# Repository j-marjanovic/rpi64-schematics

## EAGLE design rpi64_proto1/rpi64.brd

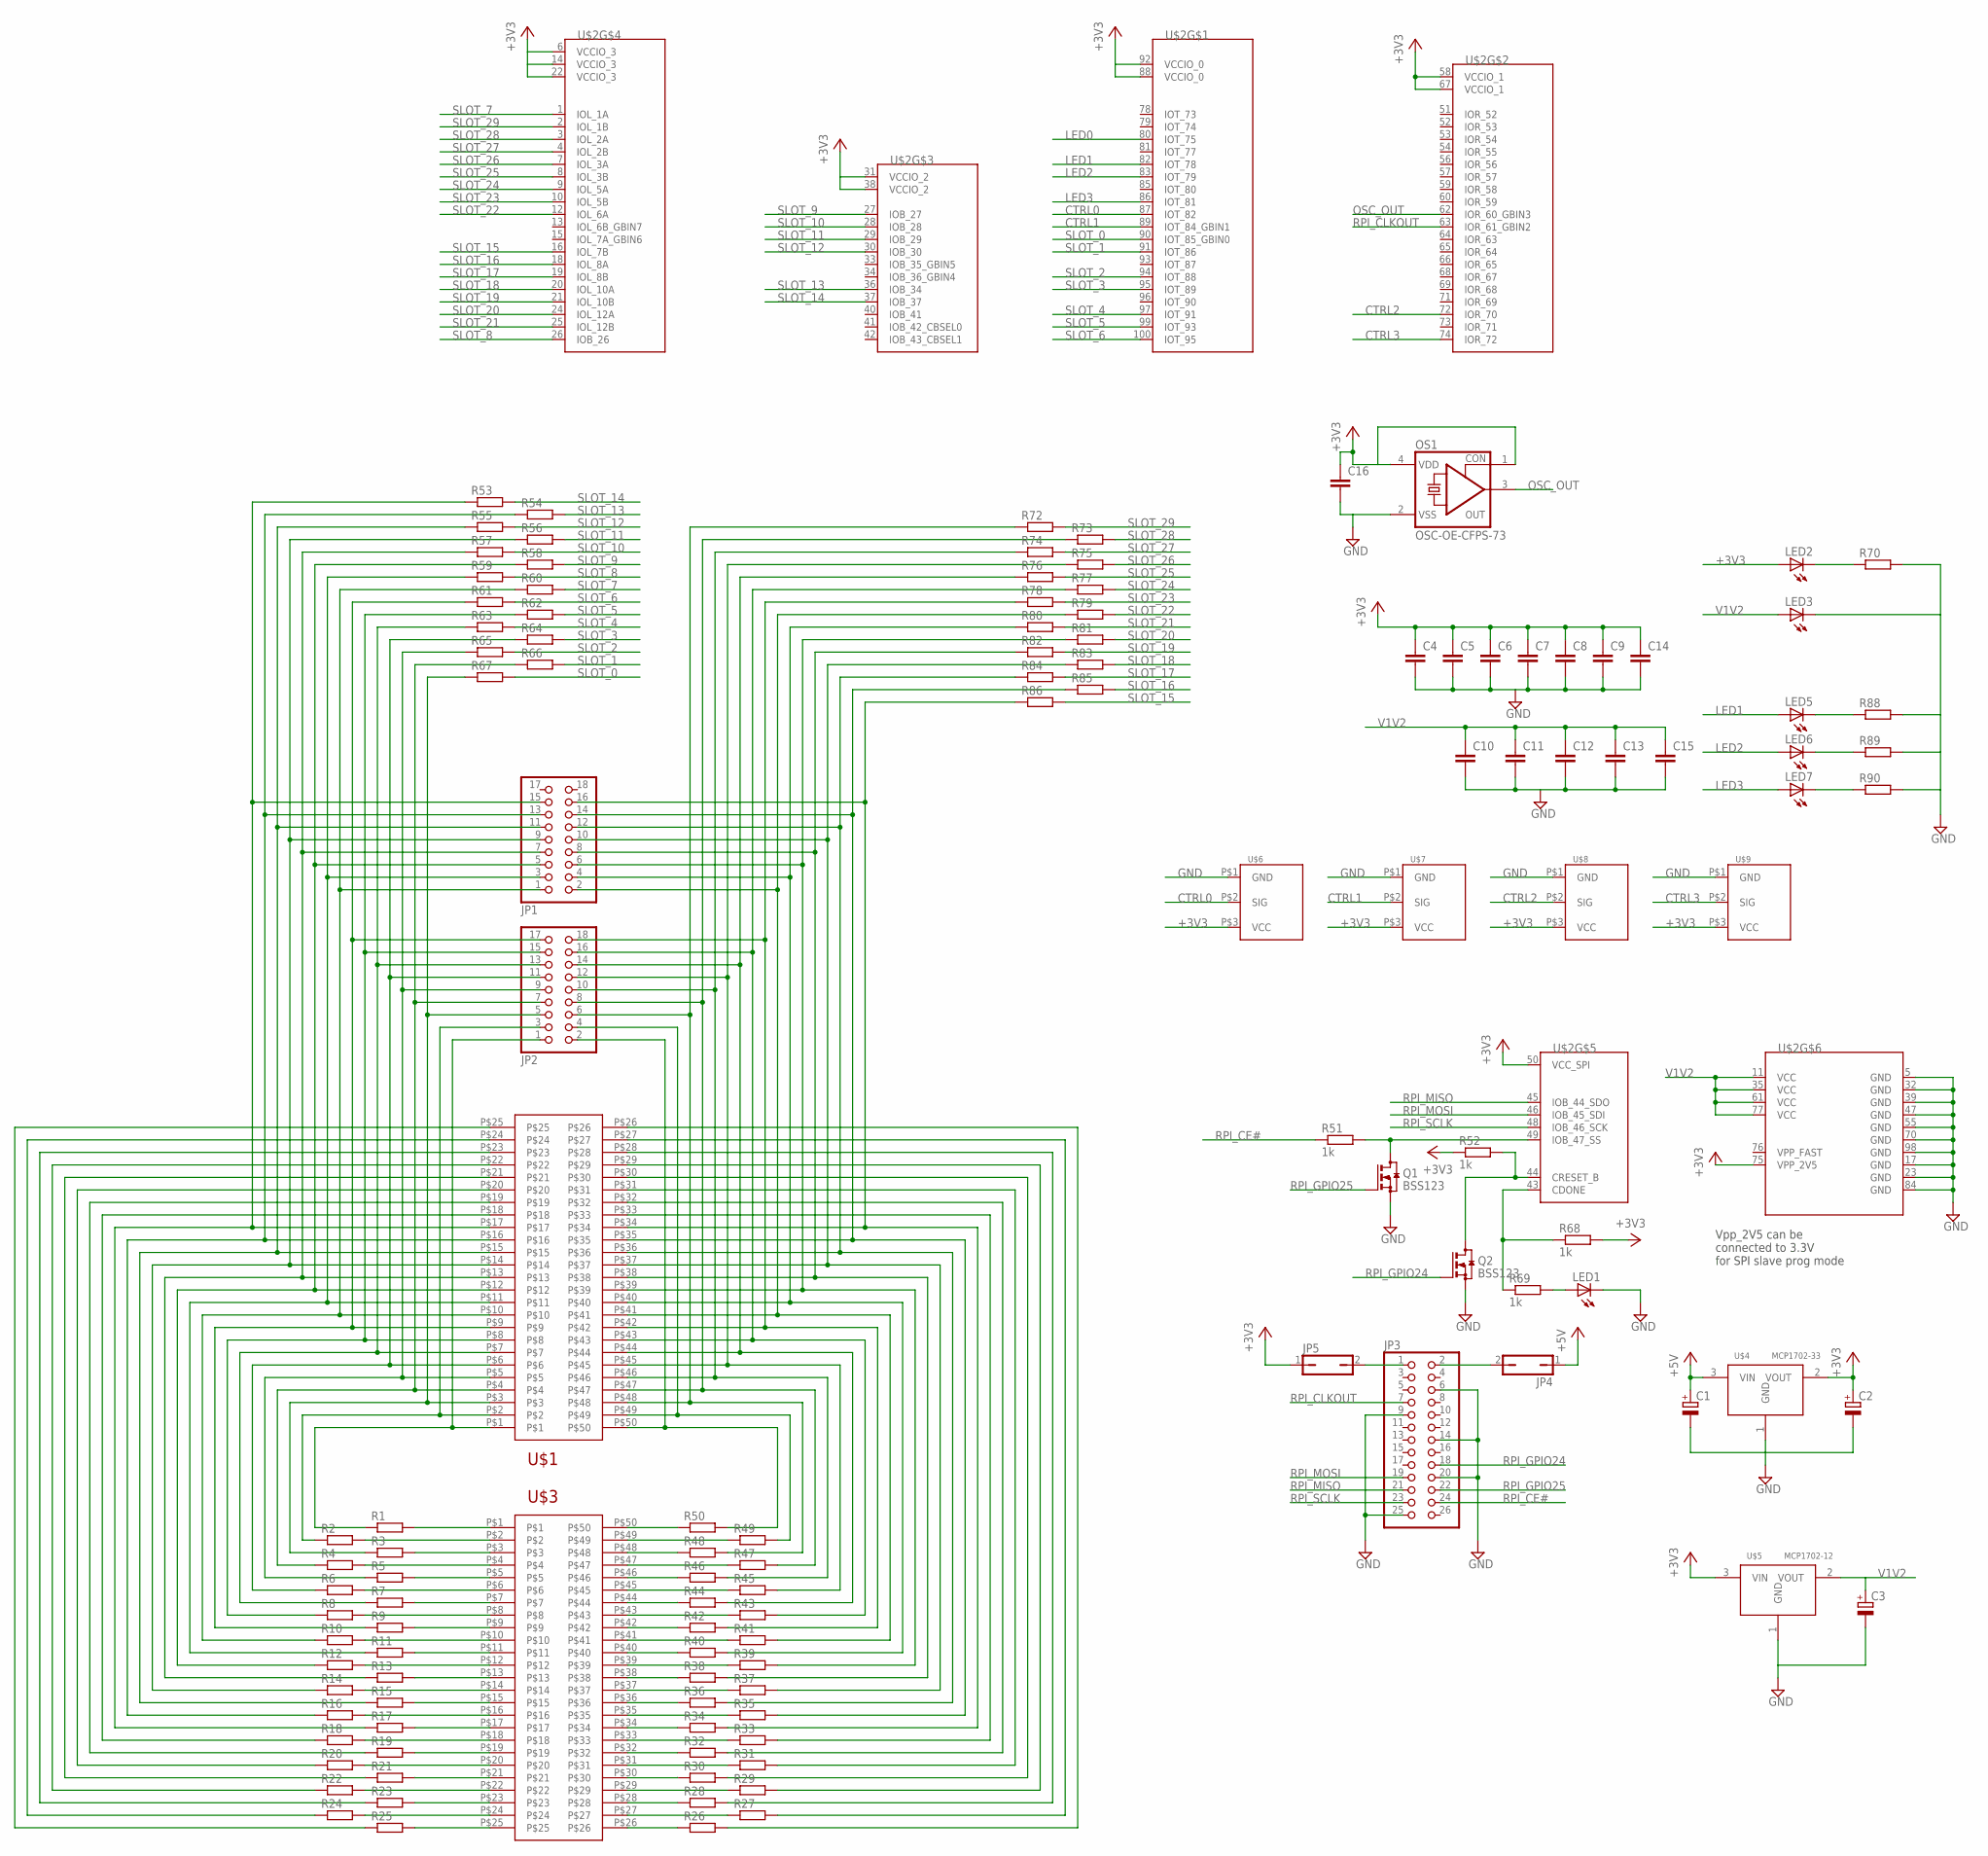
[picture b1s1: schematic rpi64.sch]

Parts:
C1, C2, C3: CPOL-EUR/2012-12R; R/2012-12R
C4, C5, C6, C7, C8, C9, C10, C11, C12, C13, C14, C15, C16: C-EUC0805; C0805
JP1, JP2: PINHD-2X9; 2X09
JP3: PINHD-2X13; 2X13
JP4, JP5: JP1Q; JP1
LED1, LED2, LED3, LED5, LED6, LED7: LEDCHIPLED_0603; CHIPLED_0603
OS1: OSC-OE-CFPS-73; 7.2X5.2-4-PAD
Q1, Q2: BSS123; SOT23
R1, R2, R3, R4, R5, R6, R7, R8, R9, R10, R11, R12, R13, R14, R15, R16, R17, R18, R19, R20, R21, R22, R23, R24, R25, R26, R27, R28, R29, R30, R31, R32, R33, R34, R35, R36, R37, R38, R39, R40, R41, R42, R43, R44, R45, R46, R47, R48, R49, R50, R53, R54, R55, R56, R57, R58, R59, R60, R61, R62, R63, R64, R65, R66, R67, R70, R72, R73, R74, R75, R76, R77, R78, R79, R80, R81, R82, R83, R84, R85, R86, R88, R89, R90: R-EU_R0603; R0603
R51, R52, R68, R69: 1k; R0603
U$1: 5530843-5; 5530843-3
U$2: ICE40HX1KVQ100; VQ100
U$3: EDGE50
U$4: MCP1702-33; SOT23A
U$5: MCP1702-12; SOT23A
U$6, U$7, U$8, U$9: N64_CONTROLER

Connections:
+3V3: C2.+, C4.1, C5.1, C6.1, C7.1, C8.1, C9.1, C14.1, C16.1, JP5.1, LED2.A, OS1.1 (CON), OS1.4 (VDD), R52.1, R68.2, U$2.6 (VCCIO_3), U$2.14 (VCCIO_3), U$2.22 (VCCIO_3), U$2.31 (VCCIO_2), U$2.38 (VCCIO_2), U$2.50 (VCC_SPI), U$2.58 (VCCIO_1), U$2.67 (VCCIO_1), U$2.75 (VPP_2V5), U$2.88 (VCCIO_0), U$2.92 (VCCIO_0), U$4.2 (VOUT), U$5.3 (VIN), U$6.P$3 (VCC), U$7.P$3 (VCC), U$8.P$3 (VCC), U$9.P$3 (VCC)
+5V: C1.+, JP4.1, U$4.3 (VIN)
CTRL0: U$2.87 (IOT_82), U$6.P$2 (SIG)
CTRL1: U$2.89 (IOT_84_GBIN1), U$7.P$2 (SIG)
CTRL2: U$2.72 (IOR_70), U$8.P$2 (SIG)
CTRL3: U$2.74 (IOR_72), U$9.P$2 (SIG)
GND: C1.-, C2.-, C3.-, C4.2, C5.2, C6.2, C7.2, C8.2, C9.2, C10.2, C11.2, C12.2, C13.2, C14.2, C15.2, C16.2, JP3.6, JP3.9, JP3.14, JP3.20, JP3.25, LED1.C, LED3.C, OS1.2 (VSS), Q1.2 (S), Q2.2 (S), R70.2, R88.2, R89.2, R90.2, U$2.5 (GND), U$2.17 (GND), U$2.23 (GND), U$2.32 (GND), U$2.39 (GND), U$2.47 (GND), U$2.55 (GND), U$2.70 (GND), U$2.84 (GND), U$2.98 (GND), U$4.1 (GND), U$5.1 (GND), U$6.P$1 (GND), U$7.P$1 (GND), U$8.P$1 (GND), U$9.P$1 (GND)
LED0: U$2.80 (IOT_75)
LED1: LED5.A, U$2.82 (IOT_78)
LED2: LED6.A, U$2.83 (IOT_79)
LED3: LED7.A, U$2.86 (IOT_81)
unnamed: R1.2, U$3.P$1
unnamed: R2.2, U$3.P$2
unnamed: R3.2, U$3.P$3
unnamed: R4.2, U$3.P$4
unnamed: R5.2, U$3.P$5
unnamed: R6.2, U$3.P$6
unnamed: R7.2, U$3.P$7
unnamed: R8.2, U$3.P$8
unnamed: R9.2, U$3.P$9
unnamed: R10.2, U$3.P$10
unnamed: R11.2, U$3.P$11
unnamed: R12.2, U$3.P$12
unnamed: R13.2, U$3.P$13
unnamed: R14.2, U$3.P$14
unnamed: R15.2, U$3.P$15
unnamed: R16.2, U$3.P$16
unnamed: R17.2, U$3.P$17
unnamed: R18.2, U$3.P$18
unnamed: R19.2, U$3.P$19
unnamed: R20.2, U$3.P$20
unnamed: R21.2, U$3.P$21
unnamed: R22.2, U$3.P$22
unnamed: R23.2, U$3.P$23
unnamed: R24.2, U$3.P$24
unnamed: R25.2, U$3.P$25
unnamed: R26.1, U$3.P$26
unnamed: R27.1, U$3.P$27
unnamed: R28.1, U$3.P$28
unnamed: R29.1, U$3.P$29
unnamed: R30.1, U$3.P$30
unnamed: R31.1, U$3.P$31
unnamed: R32.1, U$3.P$32
unnamed: R33.1, U$3.P$33
unnamed: R34.1, U$3.P$34
unnamed: R35.1, U$3.P$35
unnamed: R36.1, U$3.P$36
unnamed: R37.1, U$3.P$37
unnamed: R38.1, U$3.P$38
unnamed: R39.1, U$3.P$39
unnamed: R40.1, U$3.P$40
unnamed: R41.1, U$3.P$41
unnamed: R42.1, U$3.P$42
unnamed: R43.1, U$3.P$43
unnamed: R44.1, U$3.P$44
unnamed: R45.1, U$3.P$45
unnamed: R46.1, U$3.P$46
unnamed: R47.1, U$3.P$47
unnamed: R48.1, U$3.P$48
unnamed: R49.1, U$3.P$49
unnamed: R50.1, U$3.P$50
unnamed: JP2.1, R1.1, U$1.P$1
unnamed: JP2.3, R2.1, U$1.P$2
unnamed: JP2.5, R3.1, R67.1, U$1.P$3
unnamed: JP2.7, R4.1, R66.1, U$1.P$4
unnamed: JP2.9, R5.1, R65.1, U$1.P$5
unnamed: JP2.11, R6.1, R64.1, U$1.P$6
unnamed: JP2.13, R7.1, R63.1, U$1.P$7
unnamed: JP2.15, R8.1, R62.1, U$1.P$8
unnamed: JP2.17, R9.1, R61.1, U$1.P$9
unnamed: JP1.1, R10.1, R60.1, U$1.P$10
unnamed: JP1.3, R11.1, R59.1, U$1.P$11
unnamed: JP1.5, R12.1, R58.1, U$1.P$12
unnamed: JP1.7, R13.1, R57.1, U$1.P$13
unnamed: JP1.9, R14.1, R56.1, U$1.P$14
unnamed: JP1.11, R15.1, R55.1, U$1.P$15
unnamed: JP1.13, R16.1, R54.1, U$1.P$16
unnamed: JP1.15, R17.1, R53.1, U$1.P$17
unnamed: R18.1, U$1.P$18
unnamed: R19.1, U$1.P$19
unnamed: R20.1, U$1.P$20
unnamed: R21.1, U$1.P$21
unnamed: R22.1, U$1.P$22
unnamed: R23.1, U$1.P$23
unnamed: R24.1, U$1.P$24
unnamed: R25.1, U$1.P$25
unnamed: JP2.4, R49.2, U$1.P$49
unnamed: JP2.2, R50.2, U$1.P$50
unnamed: JP2.6, R48.2, R72.1, U$1.P$48
unnamed: JP2.8, R47.2, R73.1, U$1.P$47
unnamed: JP2.10, R46.2, R74.1, U$1.P$46
unnamed: JP2.12, R45.2, R75.1, U$1.P$45
unnamed: JP2.14, R44.2, R76.1, U$1.P$44
unnamed: JP2.16, R43.2, R77.1, U$1.P$43
unnamed: JP2.18, R42.2, R78.1, U$1.P$42
unnamed: JP1.2, R41.2, R79.1, U$1.P$41
unnamed: JP1.4, R40.2, R80.1, U$1.P$40
unnamed: JP1.6, R39.2, R81.1, U$1.P$39
unnamed: JP1.8, R38.2, R82.1, U$1.P$38
unnamed: JP1.10, R37.2, R83.1, U$1.P$37
unnamed: JP1.12, R36.2, R84.1, U$1.P$36
unnamed: R68.1, R69.1, U$2.43 (CDONE)
unnamed: JP1.16, R34.2, R86.1, U$1.P$34
unnamed: R33.2, U$1.P$33
unnamed: R32.2, U$1.P$32
unnamed: R31.2, U$1.P$31
unnamed: R30.2, U$1.P$30
unnamed: R29.2, U$1.P$29
unnamed: R28.2, U$1.P$28
unnamed: R27.2, U$1.P$27
unnamed: R26.2, U$1.P$26
unnamed: JP3.1, JP5.2
unnamed: JP3.2, JP4.2
unnamed: Q2.3 (D), R52.2, U$2.44 (CRESET_B)
unnamed: LED1.A, R69.2
unnamed: JP1.14, R35.2, R85.1, U$1.P$35
unnamed: Q1.3 (D), R51.2, U$2.49 (IOB_47_SS)
unnamed: LED7.C, R90.1
unnamed: LED6.C, R89.1
unnamed: LED5.C, R88.1
unnamed: LED2.C, R70.1
OSC_OUT: OS1.3 (OUT), U$2.62 (IOR_60_GBIN3)
RPI_CE#: JP3.24, R51.1
RPI_CLKOUT: JP3.7, U$2.63 (IOR_61_GBIN2)
RPI_GPIO24: JP3.18, Q2.1 (G)
RPI_GPIO25: JP3.22, Q1.1 (G)
RPI_MISO: JP3.21, U$2.45 (IOB_44_SDO)
RPI_MOSI: JP3.19, U$2.46 (IOB_45_SDI)
RPI_SCLK: JP3.23, U$2.48 (IOB_46_SCK)
SLOT_0: R67.2, U$2.90 (IOT_85_GBIN0)
SLOT_1: R66.2, U$2.91 (IOT_86)
SLOT_2: R65.2, U$2.94 (IOT_88)
SLOT_3: R64.2, U$2.95 (IOT_89)
SLOT_4: R63.2, U$2.97 (IOT_91)
SLOT_5: R62.2, U$2.99 (IOT_93)
SLOT_6: R61.2, U$2.100 (IOT_95)
SLOT_7: R60.2, U$2.1 (IOL_1A)
SLOT_8: R59.2, U$2.26 (IOB_26)
SLOT_9: R58.2, U$2.27 (IOB_27)
SLOT_10: R57.2, U$2.28 (IOB_28)
SLOT_11: R56.2, U$2.29 (IOB_29)
SLOT_12: R55.2, U$2.30 (IOB_30)
SLOT_13: R54.2, U$2.36 (IOB_34)
SLOT_14: R53.2, U$2.37 (IOB_37)
SLOT_15: R86.2, U$2.16 (IOL_7B)
SLOT_16: R85.2, U$2.18 (IOL_8A)
SLOT_17: R84.2, U$2.19 (IOL_8B)
SLOT_18: R83.2, U$2.20 (IOL_10A)
SLOT_19: R82.2, U$2.21 (IOL_10B)
SLOT_20: R81.2, U$2.24 (IOL_12A)
SLOT_21: R80.2, U$2.25 (IOL_12B)
SLOT_22: R79.2, U$2.12 (IOL_6A)
SLOT_23: R78.2, U$2.10 (IOL_5B)
SLOT_24: R77.2, U$2.9 (IOL_5A)
SLOT_25: R76.2, U$2.8 (IOL_3B)
SLOT_26: R75.2, U$2.7 (IOL_3A)
SLOT_27: R74.2, U$2.4 (IOL_2B)
SLOT_28: R73.2, U$2.3 (IOL_2A)
SLOT_29: R72.2, U$2.2 (IOL_1B)
V1V2: C3.+, C10.1, C11.1, C12.1, C13.1, C15.1, LED3.A, U$2.11 (VCC), U$2.35 (VCC), U$2.61 (VCC), U$2.77 (VCC), U$5.2 (VOUT)
VPP_FAST: U$2.76 (VPP_FAST)

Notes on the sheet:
Vpp_2V5 can be connected to 3.3V for SPI slave prog mode

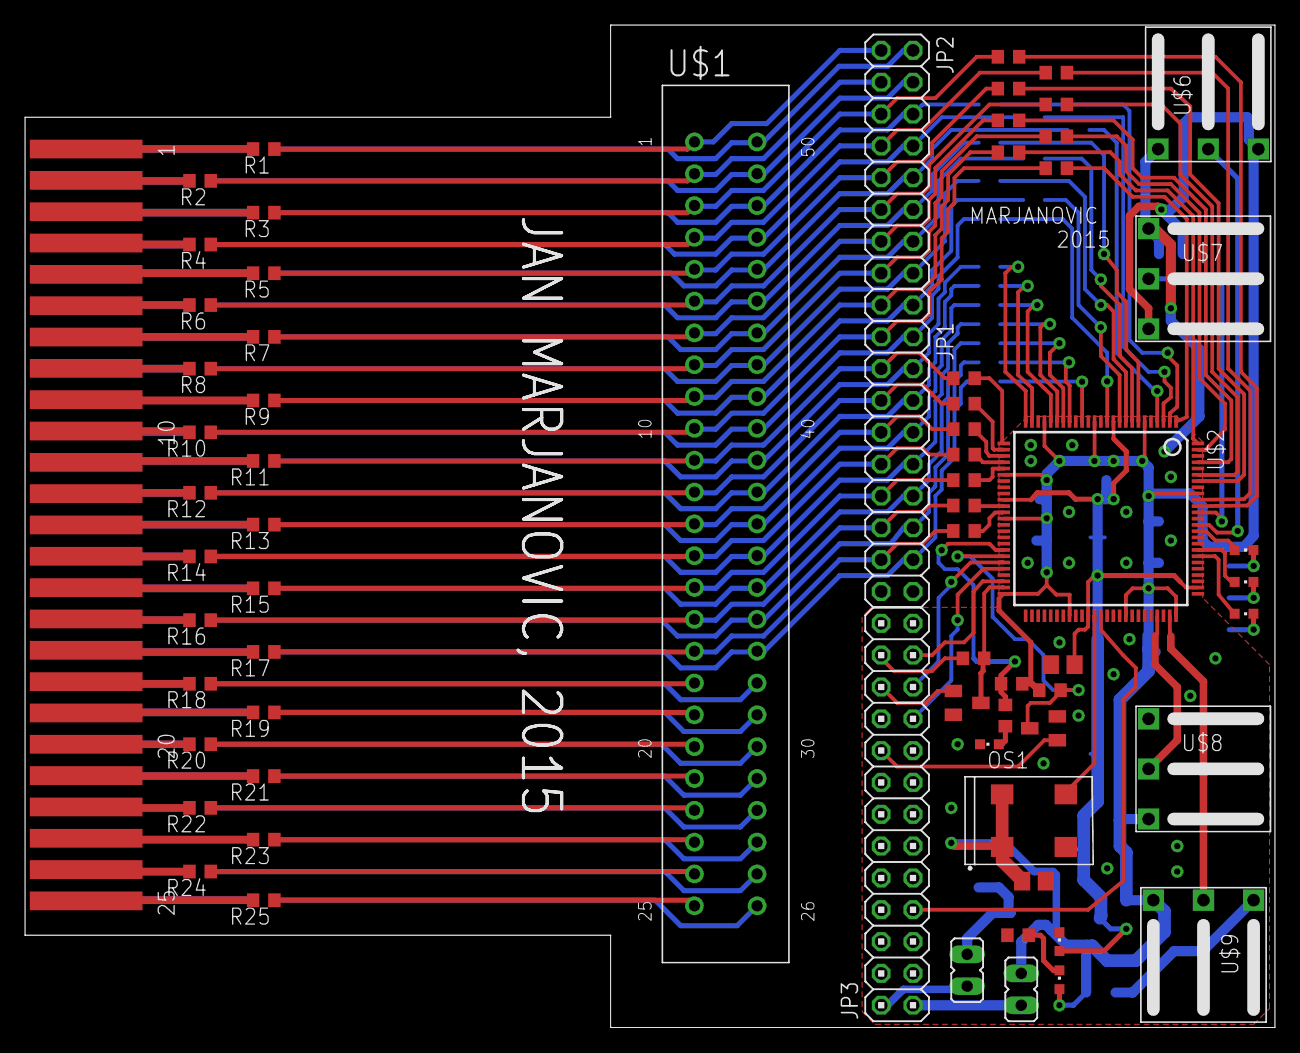
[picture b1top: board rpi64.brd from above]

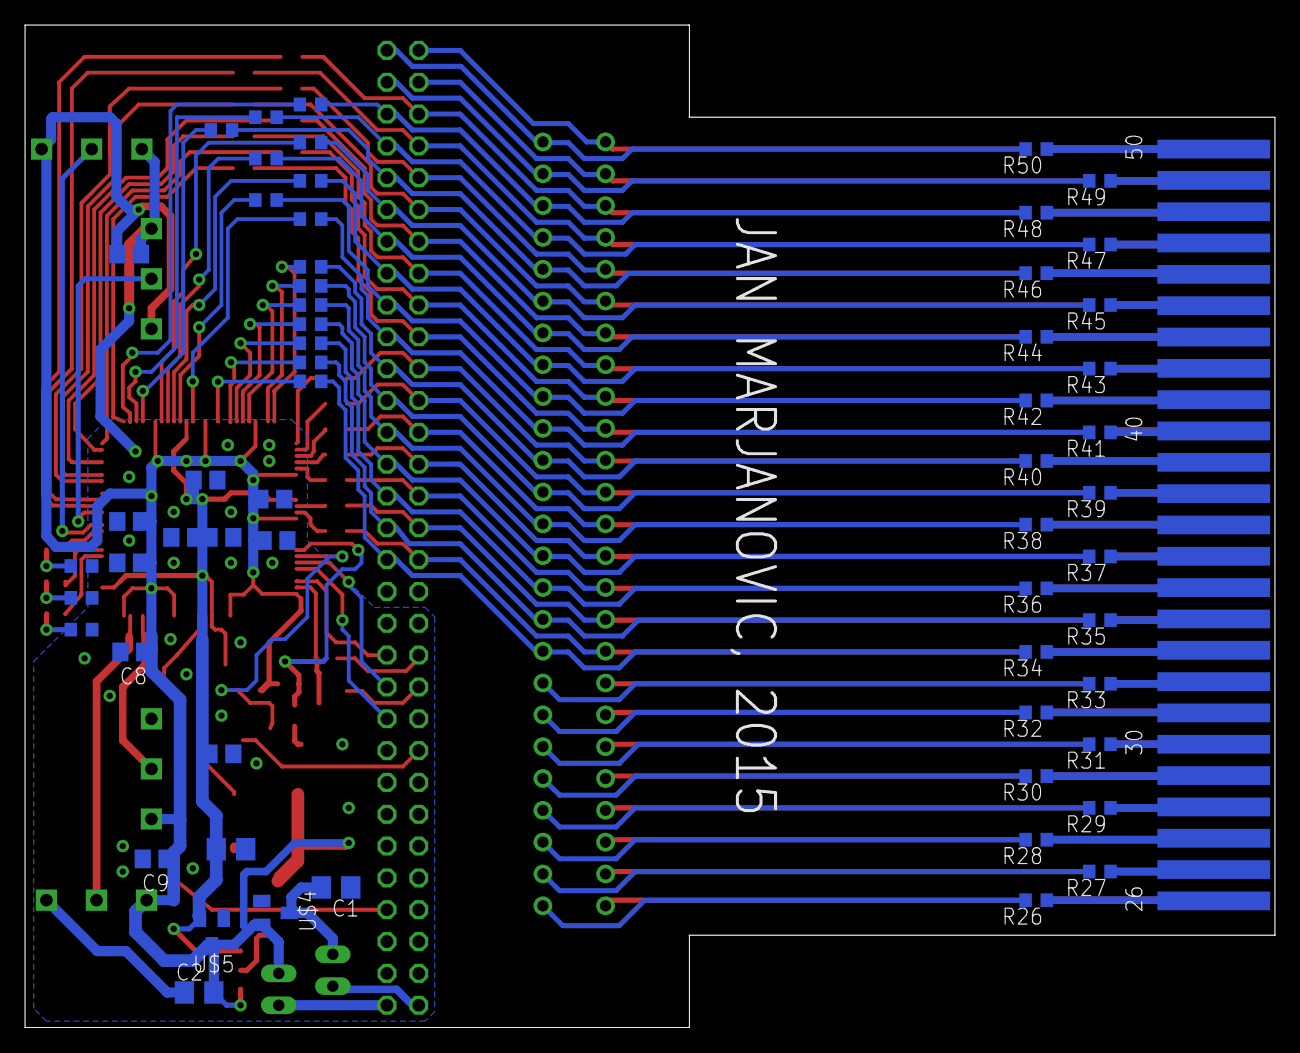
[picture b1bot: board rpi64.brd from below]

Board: 2 copper layers, 99.7 x 80.0 mm, 127 parts (59 on the bottom side), 159 nets.

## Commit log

2015-01-25 Slot and edge connector connected
2015-01-25 Added front connectors
2015-01-25 Top layer of resistor placed
2015-01-25 Placed and routed all resistor for N64 slot
2015-01-25 Added decoupling capacitors
2015-01-25 Added clocks
2015-01-26 Everything placed and routed
2015-01-26 Resolved DRC problems
2015-01-27 First prototype
2015-02-22 Added bom
